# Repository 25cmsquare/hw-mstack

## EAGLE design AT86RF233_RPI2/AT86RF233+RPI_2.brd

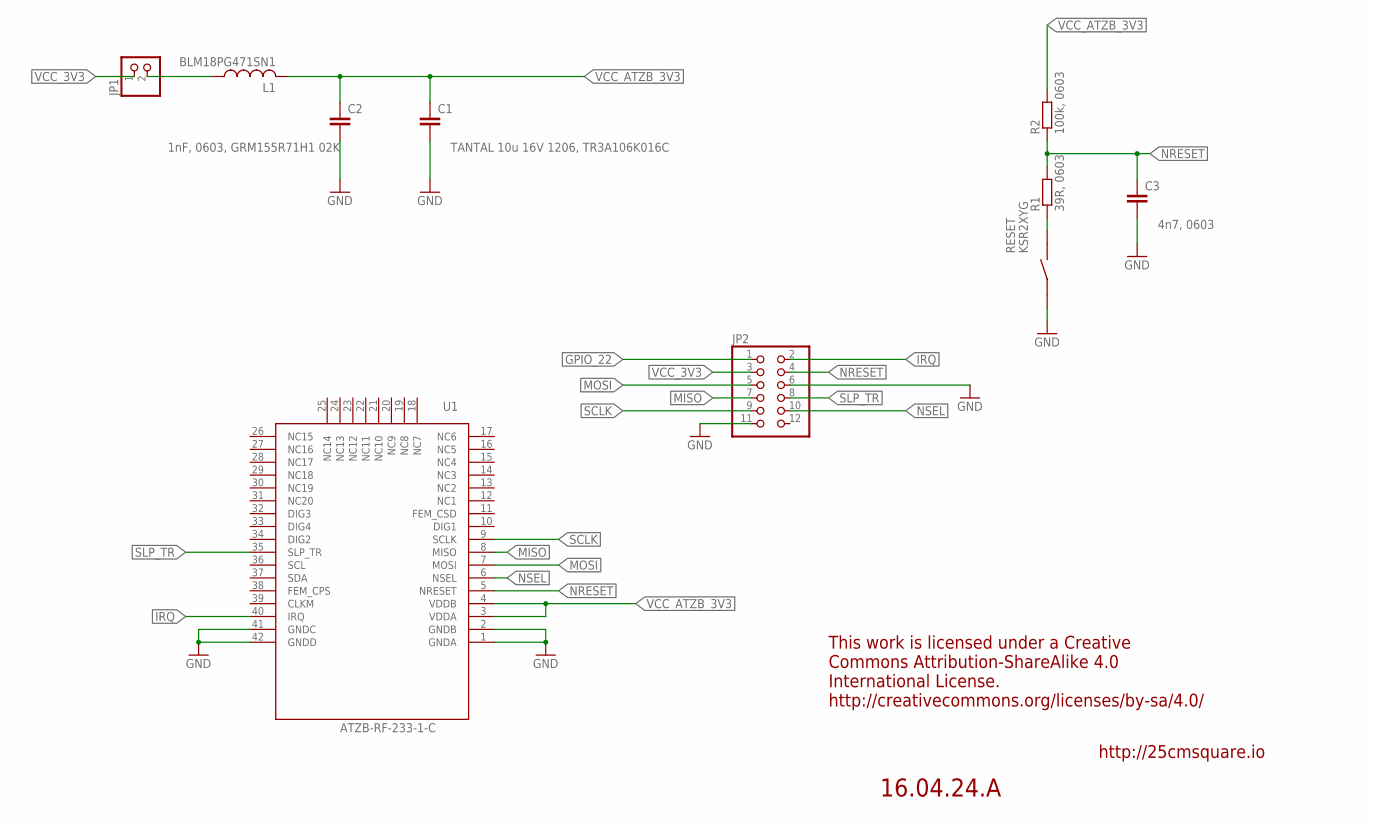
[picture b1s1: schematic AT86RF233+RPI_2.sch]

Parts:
C1: TANTAL 10u 16V 1206, TR3A106K016C; C1206K
C2: 1nF, 0603, GRM155R71H1 02K; C0603K
C3: 4n7, 0603; C0603K
JP1: PINHD-1X2; 1X02
JP2: PINHD-2X6; 2X06
L1: BLM18PG471SN1; L0603
R1: 39R, 0603; R0603
R2: 100k, 0603; R0603
RESET: KSR2XYG
U1: ATZB-RF-233-1-C

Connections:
GND: C1.2, C2.2, C3.2, JP2.6, JP2.11, RESET.P$2 (2), U1.1 (GNDA), U1.2 (GNDB), U1.41 (GNDC), U1.42 (GNDD)
GPIO_22: JP2.1
IRQ: JP2.2, U1.40 (IRQ)
MISO: JP2.7, U1.8 (MISO)
MOSI: JP2.5, U1.7 (MOSI)
unnamed: R1.1, RESET.P$1 (1)
unnamed: JP1.2, L1.1
NRESET: C3.1, JP2.4, R1.2, R2.1, U1.5 (NRESET)
NSEL: JP2.10, U1.6 (NSEL)
SCLK: JP2.9, U1.9 (SCLK)
SLP_TR: JP2.8, U1.35 (SLP_TR)
VCC_3V3: JP1.1, JP2.3
VCC_ATZB_3V3: C1.1, C2.1, L1.2, R2.2, U1.3 (VDDA), U1.4 (VDDB)

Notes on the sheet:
This work is licensed under a Creative Commons Attribution-ShareAlike 4.0 International License. http://creativecommons.org/licenses/by-sa/4.0/
http://25cmsquare.io
16.04.24.A

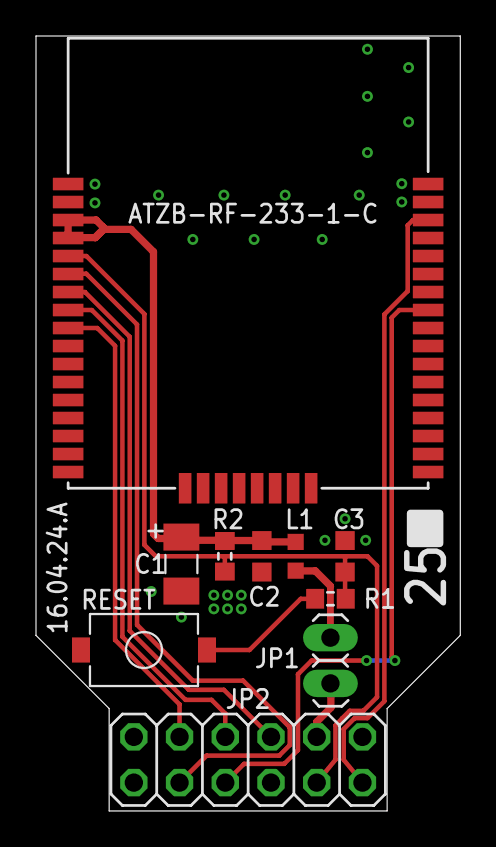
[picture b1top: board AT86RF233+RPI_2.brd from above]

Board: 2 copper layers, 23.6 x 43.1 mm, 10 parts (0 on the bottom side), 12 nets.

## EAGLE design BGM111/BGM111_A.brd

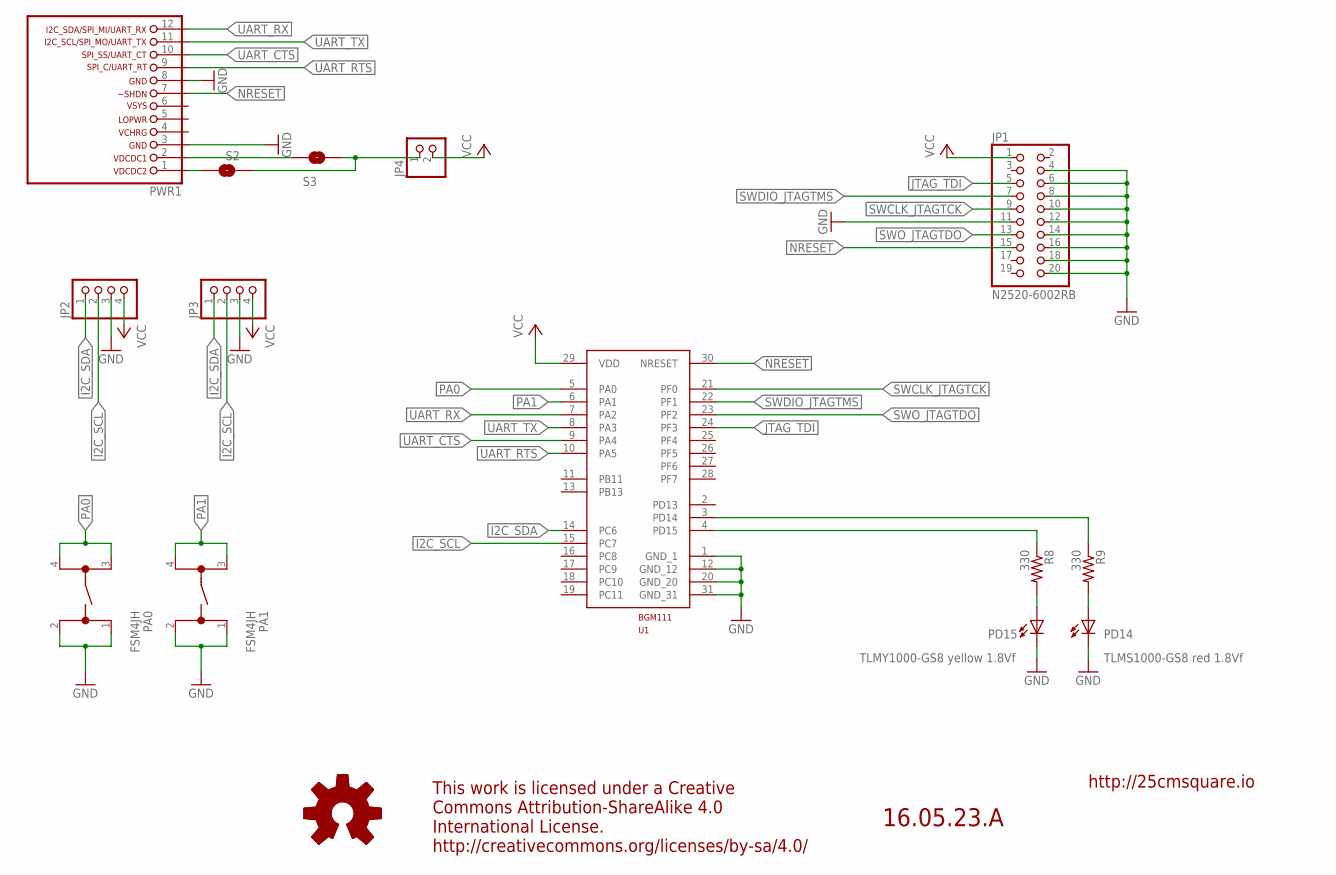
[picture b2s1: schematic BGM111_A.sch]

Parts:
JP1: N2520-6002RB; 2X10
JP2, JP3: PINHD-1X4; 1X04
JP4: PINHD-1X2; 1X02
PA0, PA1: FSM4JH
PD14: TLMS1000-GS8 red 1.8Vf; SML0603
PD15: TLMY1000-GS8 yellow 1.8Vf; SML0603
PWR1: LIWE_12_PIN_PWR; LIWE_12_PIN
R8, R9: 330; R0603
S2, S3: SOLDERJUMPERNC2; SJ_2S-NOTRACE
U1: BGM111
U$1: OSHW_LOGO; OSHW

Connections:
GND: JP1.4, JP1.6, JP1.8, JP1.10, JP1.11, JP1.12, JP1.14, JP1.16, JP1.18, JP1.20, JP2.3, JP3.3, PA0.1, PA0.2, PA1.1, PA1.2, PD14.C, PD15.C, PWR1.3, PWR1.8, U1.1 (GND_1), U1.12 (GND_12), U1.20 (GND_20), U1.31 (GND_31)
I2C_SCL: JP2.2, JP3.2, U1.15 (PC7)
I2C_SDA: JP2.1, JP3.1, U1.14 (PC6)
JTAG_TDI: JP1.5, U1.24 (PF3)
unnamed: PWR1.1, S2.1
unnamed: PWR1.2, S3.1
unnamed: JP4.1, S2.2, S3.2
unnamed: PD14.A, R9.2
unnamed: PD15.A, R8.2
NRESET: JP1.15, PWR1.7, U1.30 (NRESET)
PA0: PA0.3, PA0.4, U1.5 (PA0)
PA1: PA1.3, PA1.4, U1.6 (PA1)
PF5: R9.1, U1.3 (PD14)
PF6: R8.1, U1.4 (PD15)
SWCLK_JTAGTCK: JP1.9, U1.21 (PF0)
SWDIO_JTAGTMS: JP1.7, U1.22 (PF1)
SWO_JTAGTDO: JP1.13, U1.23 (PF2)
UART_CTS: PWR1.10, U1.9 (PA4)
UART_RTS: PWR1.9, U1.10 (PA5)
UART_RX: PWR1.12, U1.7 (PA2)
UART_TX: PWR1.11, U1.8 (PA3)
VCC: JP1.1, JP2.4, JP3.4, JP4.2, U1.29 (VDD)

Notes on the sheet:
This work is licensed under a Creative Commons Attribution-ShareAlike 4.0 International License. http://creativecommons.org/licenses/by-sa/4.0/
16.05.23.A
http://25cmsquare.io

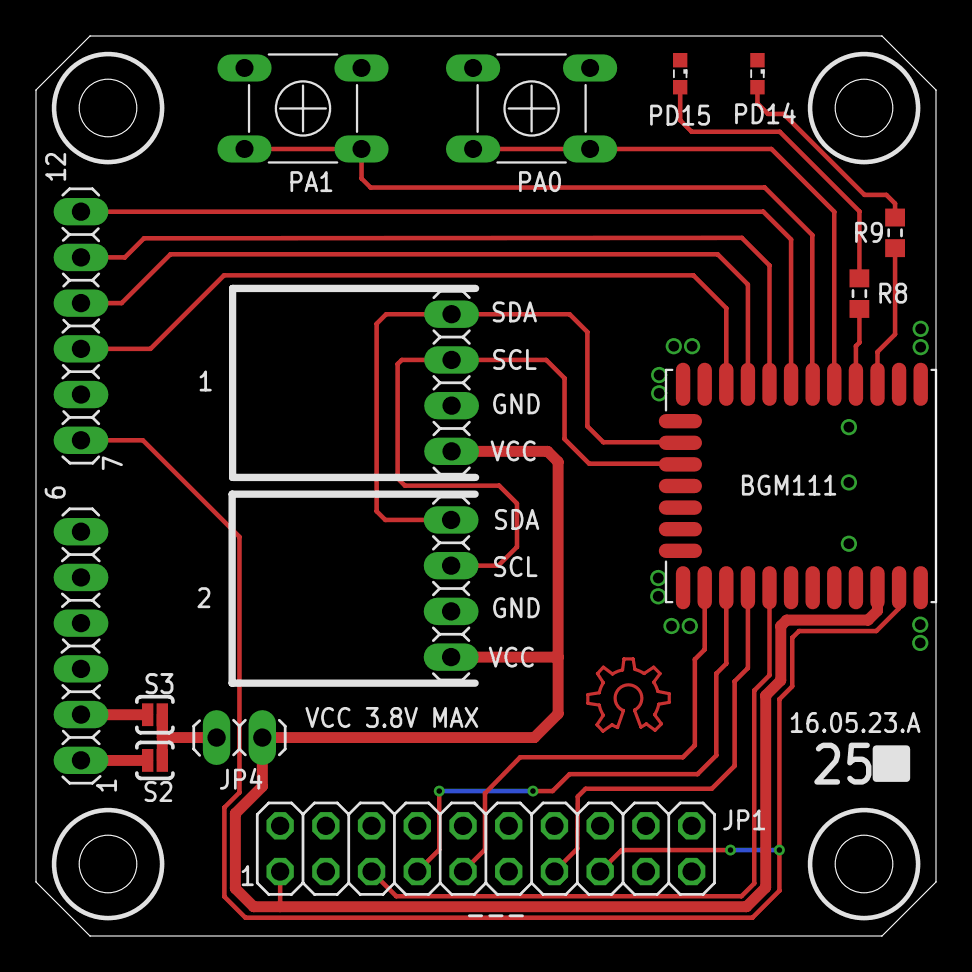
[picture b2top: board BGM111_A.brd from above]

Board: 2 copper layers, 50.0 x 50.0 mm, 15 parts (0 on the bottom side), 22 nets.

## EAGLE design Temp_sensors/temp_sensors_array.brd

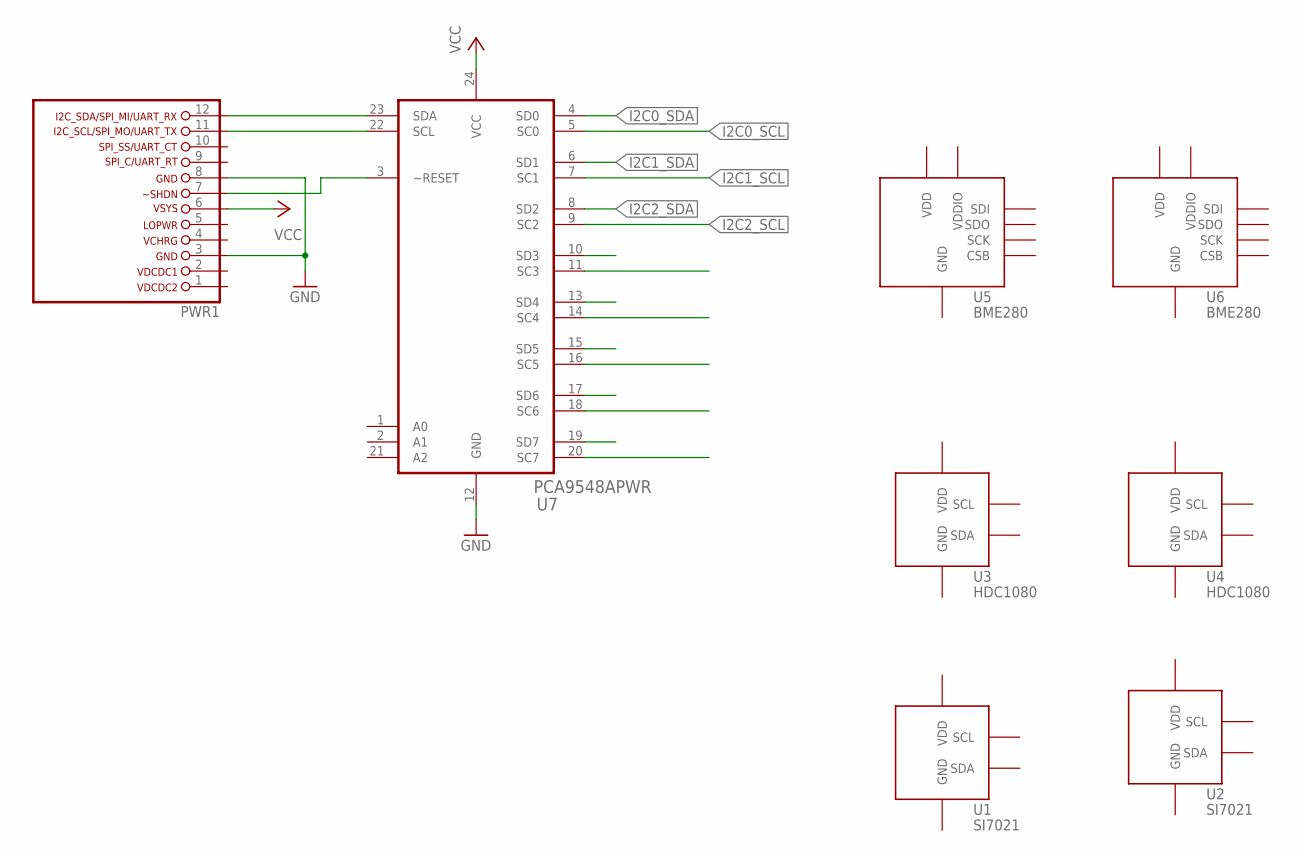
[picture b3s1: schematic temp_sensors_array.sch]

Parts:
PWR1: LIWE_12_PIN_PWR; LIWE_12_PIN
U1, U2: SI7021
U3, U4: HDC1080; SI7021
U5, U6: BME280; BME1080
U7: PCA9548APWR; SOP65P640X120-24N

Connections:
GND: PWR1.3, PWR1.8, U1.2 (GND), U2.2 (GND), U3.2 (GND), U4.2 (GND), U5.1 (GND), U5.7 (GND), U6.1 (GND), U6.7 (GND), U7.12 (GND)
I2C0_SCL: U7.5 (SC0)
I2C0_SDA: U7.4 (SD0)
I2C1_SCL: U7.7 (SC1)
I2C1_SDA: U7.6 (SD1)
I2C2_SCL: U7.9 (SC2)
I2C2_SDA: U7.8 (SD2)
unnamed: PWR1.12, U7.23 (SDA)
unnamed: PWR1.11, U7.22 (SCL)
unnamed: PWR1.7, U7.3 (~RESET)
VCC: PWR1.6, U7.24 (VCC)
VDD: U1.5 (VDD), U2.5 (VDD), U3.5 (VDD), U4.5 (VDD), U5.8 (VDD), U6.8 (VDD)
VDDIO: U5.6 (VDDIO), U6.6 (VDDIO)

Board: 2 copper layers, 8 parts (0 on the bottom side), 7 nets, no tracks yet.

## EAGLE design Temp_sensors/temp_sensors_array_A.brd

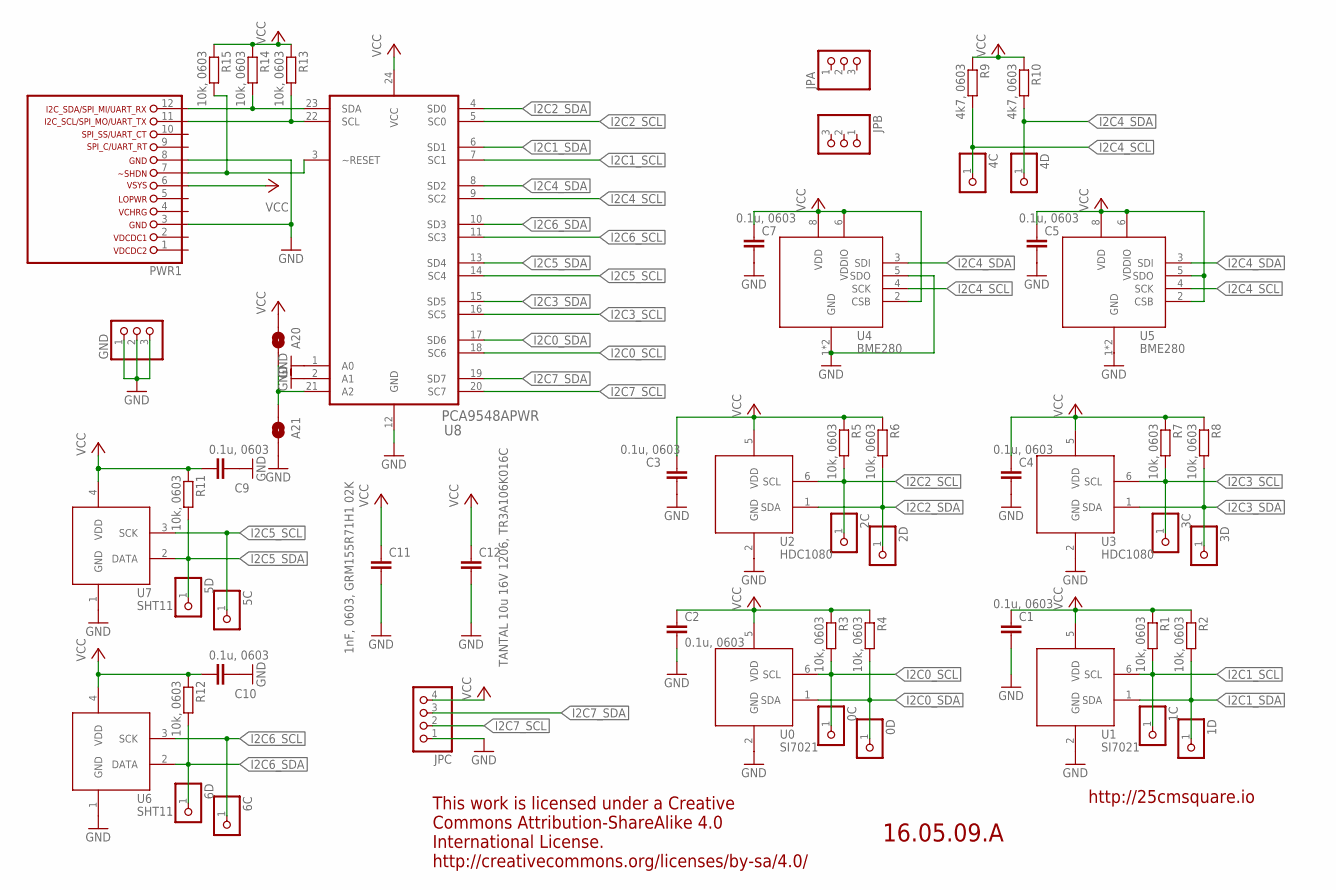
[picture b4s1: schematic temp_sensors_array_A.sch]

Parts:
0C, 0D, 1C, 1D, 2C, 2D, 3C, 3D, 4C, 4D, 5C, 5D, 6C, 6D: PINHD-1X1; 1X01
A20, A21: SOLDERJUMPERNO; SJ_2S-NO
C1, C2, C3, C4, C5, C7, C9, C10: 0.1u, 0603; C0603K
C11: 1nF, 0603, GRM155R71H1 02K; C0603K
C12: TANTAL 10u 16V 1206, TR3A106K016C; C1206K
GND: PINHD-1X3; 1X03
JPA: PINHD-1X3; 1X03
JPB: PINHD-1X3; 1X03
JPC: PINHD-1X4; 1X04
PWR1: LIWE_12_PIN_PWR; LIWE_12_PIN
R1, R2, R3, R4, R5, R6, R7, R8, R11, R12, R13, R14, R15: 10k, 0603; R0603
R9, R10: 4k7, 0603; R0603
U0, U1: SI7021
U2, U3: HDC1080; SI7021
U4, U5: BME280; BME1080
U6, U7: SHT11; SHT1X
U8: PCA9548APWR; SOP65P640X120-24N

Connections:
GND: A21.2, C1.2, C2.2, C3.2, C4.2, C5.2, C7.2, C9.2, C10.2, C11.2, C12.2, GND.1, GND.2, GND.3, JPC.1, PWR1.3, PWR1.8, U0.2 (GND), U1.2 (GND), U2.2 (GND), U3.2 (GND), U4.1 (GND), U4.5 (SDO), U4.7 (GND), U5.1 (GND), U5.7 (GND), U6.1 (GND), U7.1 (GND), U8.1 (A0), U8.2 (A1), U8.12 (GND)
I2C0_SCL: 0C.1, R3.2, U0.6 (SCL), U8.18 (SC6)
I2C0_SDA: 0D.1, R4.2, U0.1 (SDA), U8.17 (SD6)
I2C1_SCL: 1C.1, R1.2, U1.6 (SCL), U8.7 (SC1)
I2C1_SDA: 1D.1, R2.2, U1.1 (SDA), U8.6 (SD1)
I2C2_SCL: 2C.1, R5.2, U2.6 (SCL), U8.5 (SC0)
I2C2_SDA: 2D.1, R6.2, U2.1 (SDA), U8.4 (SD0)
I2C3_SCL: 3C.1, R7.2, U3.6 (SCL), U8.16 (SC5)
I2C3_SDA: 3D.1, R8.2, U3.1 (SDA), U8.15 (SD5)
I2C4_SCL: 4C.1, R9.2, U4.4 (SCK), U5.4 (SCK), U8.9 (SC2)
I2C4_SDA: 4D.1, R10.2, U4.3 (SDI), U5.3 (SDI), U8.8 (SD2)
I2C5_SCL: 5C.1, U7.3 (SCK), U8.14 (SC4)
I2C5_SDA: 5D.1, R11.2, U7.2 (DATA), U8.13 (SD4)
I2C6_SCL: 6C.1, U6.3 (SCK), U8.11 (SC3)
I2C6_SDA: 6D.1, R12.2, U6.2 (DATA), U8.10 (SD3)
I2C7_SCL: JPC.2, U8.20 (SC7)
I2C7_SDA: JPC.3, U8.19 (SD7)
unnamed: A20.2, A21.1, U8.21 (A2)
NRESET: PWR1.7, R15.2, U8.3 (~RESET)
SCL: PWR1.11, R13.2, U8.22 (SCL)
SDA: PWR1.12, R14.2, U8.23 (SDA)
VCC: A20.1, C1.1, C2.1, C3.1, C4.1, C5.1, C7.1, C9.1, C10.1, C11.1, C12.1, JPC.4, PWR1.6, R1.1, R2.1, R3.1, R4.1, R5.1, R6.1, R7.1, R8.1, R9.1, R10.1, R11.1, R12.1, R13.1, R14.1, R15.1, U0.5 (VDD), U1.5 (VDD), U2.5 (VDD), U3.5 (VDD), U4.2 (CSB), U4.6 (VDDIO), U4.8 (VDD), U5.2 (CSB), U5.5 (SDO), U5.6 (VDDIO), U5.8 (VDD), U6.4 (VDD), U7.4 (VDD), U8.24 (VCC)

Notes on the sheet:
This work is licensed under a Creative Commons Attribution-ShareAlike 4.0 International License. http://creativecommons.org/licenses/by-sa/4.0/
16.05.09.A
http://25cmsquare.io

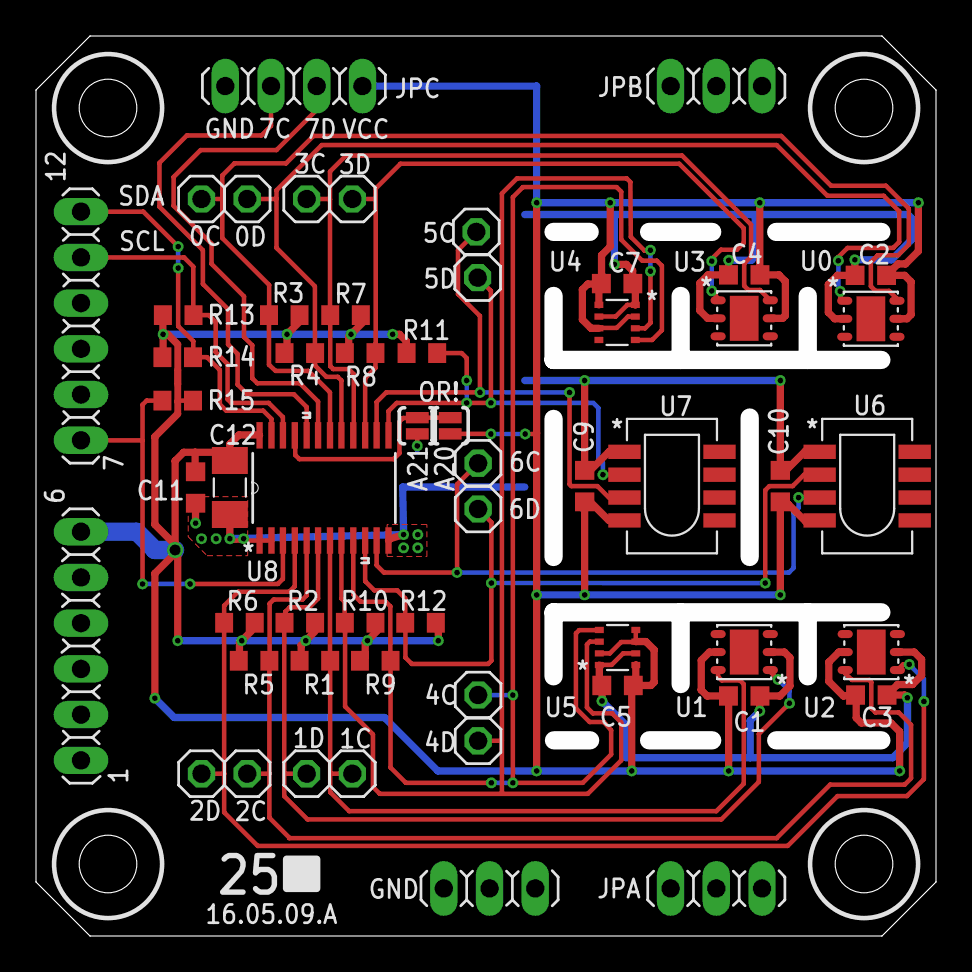
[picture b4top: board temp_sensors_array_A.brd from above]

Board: 2 copper layers, 50.0 x 50.0 mm, 55 parts (0 on the bottom side), 22 nets.

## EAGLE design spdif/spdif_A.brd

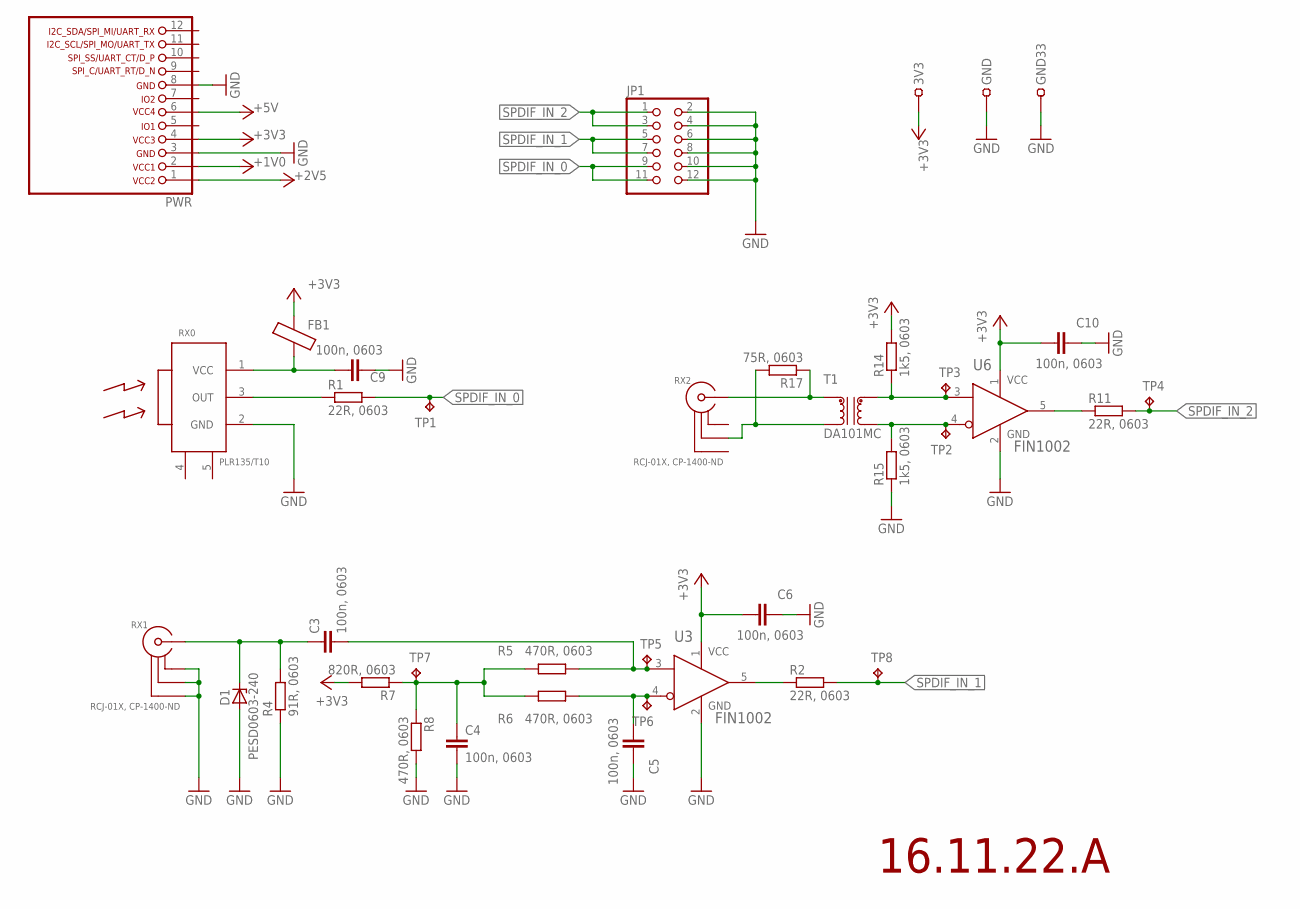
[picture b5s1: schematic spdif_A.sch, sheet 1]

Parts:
3V3: TEST-22-MULTICOMP; TEST_1MM
C3, C4, C5, C6, C9, C10: 100n, 0603; C0603
D1: PESD0603-240; L0603
FB1: FB_0603; L0603
GND, GND33: TEST-22-MULTICOMP; TEST_1MM
JP1: PINHD-2X6/90; 2X06/90
PWR: LIWE_12_PIN_PWR7X7_COMPAT; LIWE_12_PIN_7X7_COMPAT
R1, R2, R11: 22R, 0603; R0603
R4: 91R, 0603; R0603
R5, R6, R8: 470R, 0603; R0603
R7: 820R, 0603; R0603
R14, R15: 1k5, 0603; R0603
R17: 75R, 0603; R0603
RX0: PLR135/T10; PLR135_T10
RX1, RX2: RCJ-01X, CP-1400-ND; RCJ-01X
T1: DA101MC
TP1, TP2, TP3, TP4, TP5, TP6, TP7, TP8: TPB1,27; B1,27
U3, U6: FIN1002; SOT95P280X140-5N

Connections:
+1V0: PWR.2
+2V5: PWR.1
+3V3: 3V3.1, C6.2, C10.2, FB1.2, PWR.4, R7.2, R14.2, U3.1 (VCC), U6.1 (VCC); also elsewhere on the board
+5V: PWR.6
GND: C4.2, C5.1, C6.1, C9.1, C10.1, D1.1 (A), GND.1, GND33.1, JP1.2, JP1.4, JP1.6, JP1.8, JP1.10, JP1.12, PWR.3, PWR.8, R4.1, R8.2, R15.1, RX0.2 (GND), RX1.20 (GND1), RX1.21 (GND2), RX1.22 (GND3), U3.2 (GND), U6.2 (GND); also elsewhere on the board
unnamed: R2.1, U3.5 (ROUT)
unnamed: C3.2, R5.1, TP5.TP, U3.3 (RIN+)
unnamed: C9.2, FB1.1, RX0.1 (VCC)
unnamed: C3.1, D1.2 (C), R4.2, RX1.1 (SIG)
unnamed: R11.1, U6.5 (ROUT)
unnamed: C4.1, R5.2, R6.2, R7.1, R8.1, TP7.TP
unnamed: C5.2, R6.1, TP6.TP, U3.4 (RIN-)
unnamed: R15.2, T1.4, TP2.TP, U6.4 (RIN-)
unnamed: R14.1, T1.6, TP3.TP, U6.3 (RIN+)
unnamed: R17.2, RX2.21 (GND2), T1.3
unnamed: R17.1, RX2.1 (SIG), T1.1
SPDIF0_IN: R1.1, RX0.3 (OUT)
SPDIF_IN_0: JP1.9, JP1.11, R1.2, TP1.TP
SPDIF_IN_1: JP1.5, JP1.7, R2.2, TP8.TP
SPDIF_IN_2: JP1.1, JP1.3, R11.2, TP4.TP

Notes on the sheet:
16.11.22.A

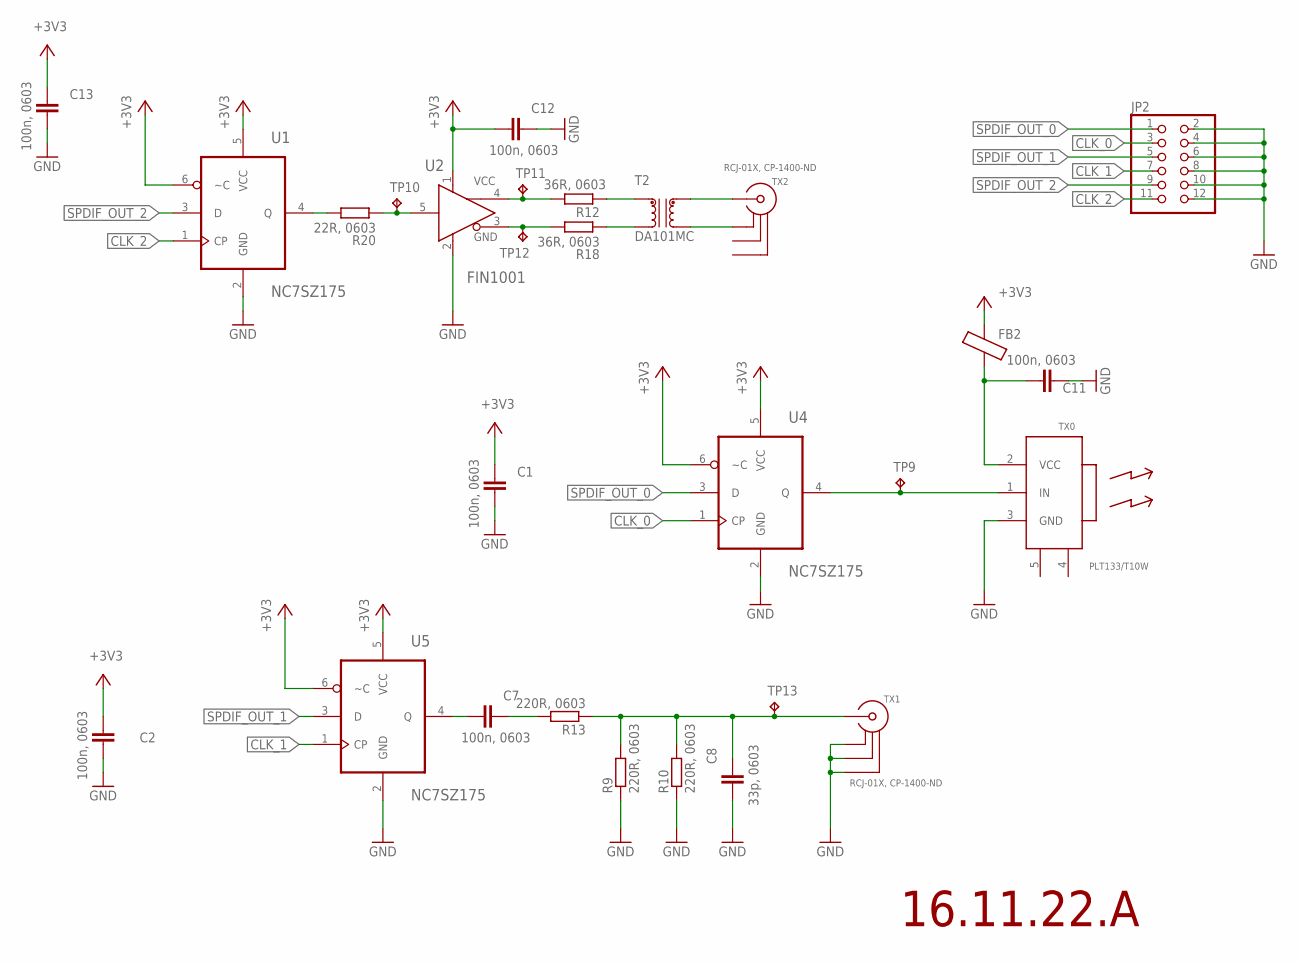
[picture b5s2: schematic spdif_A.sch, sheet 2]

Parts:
C1, C2, C7, C11, C12, C13: 100n, 0603; C0603
C8: 33p, 0603; C0603
FB2: FB_0603; L0603
JP2: PINHD-2X6/90; 2X06/90
R9, R10, R13: 220R, 0603; R0603
R12, R18: 36R, 0603; R0603
R20: 22R, 0603; R0603
T2: DA101MC
TP9, TP10, TP11, TP12, TP13: TPB1,27; B1,27
TX0: PLT133/T10W; PLT133_T10W
TX1, TX2: RCJ-01X, CP-1400-ND; RCJ-01X
U1, U4, U5: NC7SZ175; SOT65P210X110-6N
U2: FIN1001; SOT95P280X140-5N

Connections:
+3V3: C1.2, C2.2, C12.2, C13.2, FB2.2, U1.5 (VCC), U1.6 (~C), U2.1 (VCC), U4.5 (VCC), U4.6 (~C), U5.5 (VCC), U5.6 (~C); also elsewhere on the board
CLK_0: JP2.3, U4.1 (CP)
CLK_1: JP2.7, U5.1 (CP)
CLK_2: JP2.11, U1.1 (CP)
DA_N: R18.1, T2.3
DA_P: R12.1, T2.1
FIN_IN: R20.1, TP10.TP, U2.5 (RIN)
FIN_OUT_N: R18.2, TP12.TP, U2.3 (ROUT-)
FIN_OUT_P: R12.2, TP11.TP, U2.4 (ROUT+)
GND: C1.1, C2.1, C8.2, C11.1, C12.1, C13.1, JP2.2, JP2.4, JP2.6, JP2.8, JP2.10, JP2.12, R9.1, R10.1, TX0.3 (GND), TX1.20 (GND1), TX1.21 (GND2), TX1.22 (GND3), U1.2 (GND), U2.2 (GND), U4.2 (GND), U5.2 (GND); also elsewhere on the board
unnamed: C8.1, R9.2, R10.2, R13.1, TP13.TP, TX1.1 (SIG)
unnamed: C7.1, R13.2
unnamed: C7.2, U5.4 (Q)
Q: R20.2, U1.4 (Q)
SPDIF_OUT_0: JP2.1, U4.3 (D)
SPDIF_OUT_1: JP2.5, U5.3 (D)
SPDIF_OUT_2: JP2.9, U1.3 (D)
TX0_IN: TP9.TP, TX0.1 (IN), U4.4 (Q)
TX0_VCC: C11.2, FB2.1, TX0.2 (VCC)
TX2_N: T2.4, TX2.20 (GND1)
TX2_P: T2.6, TX2.1 (SIG)

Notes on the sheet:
16.11.22.A

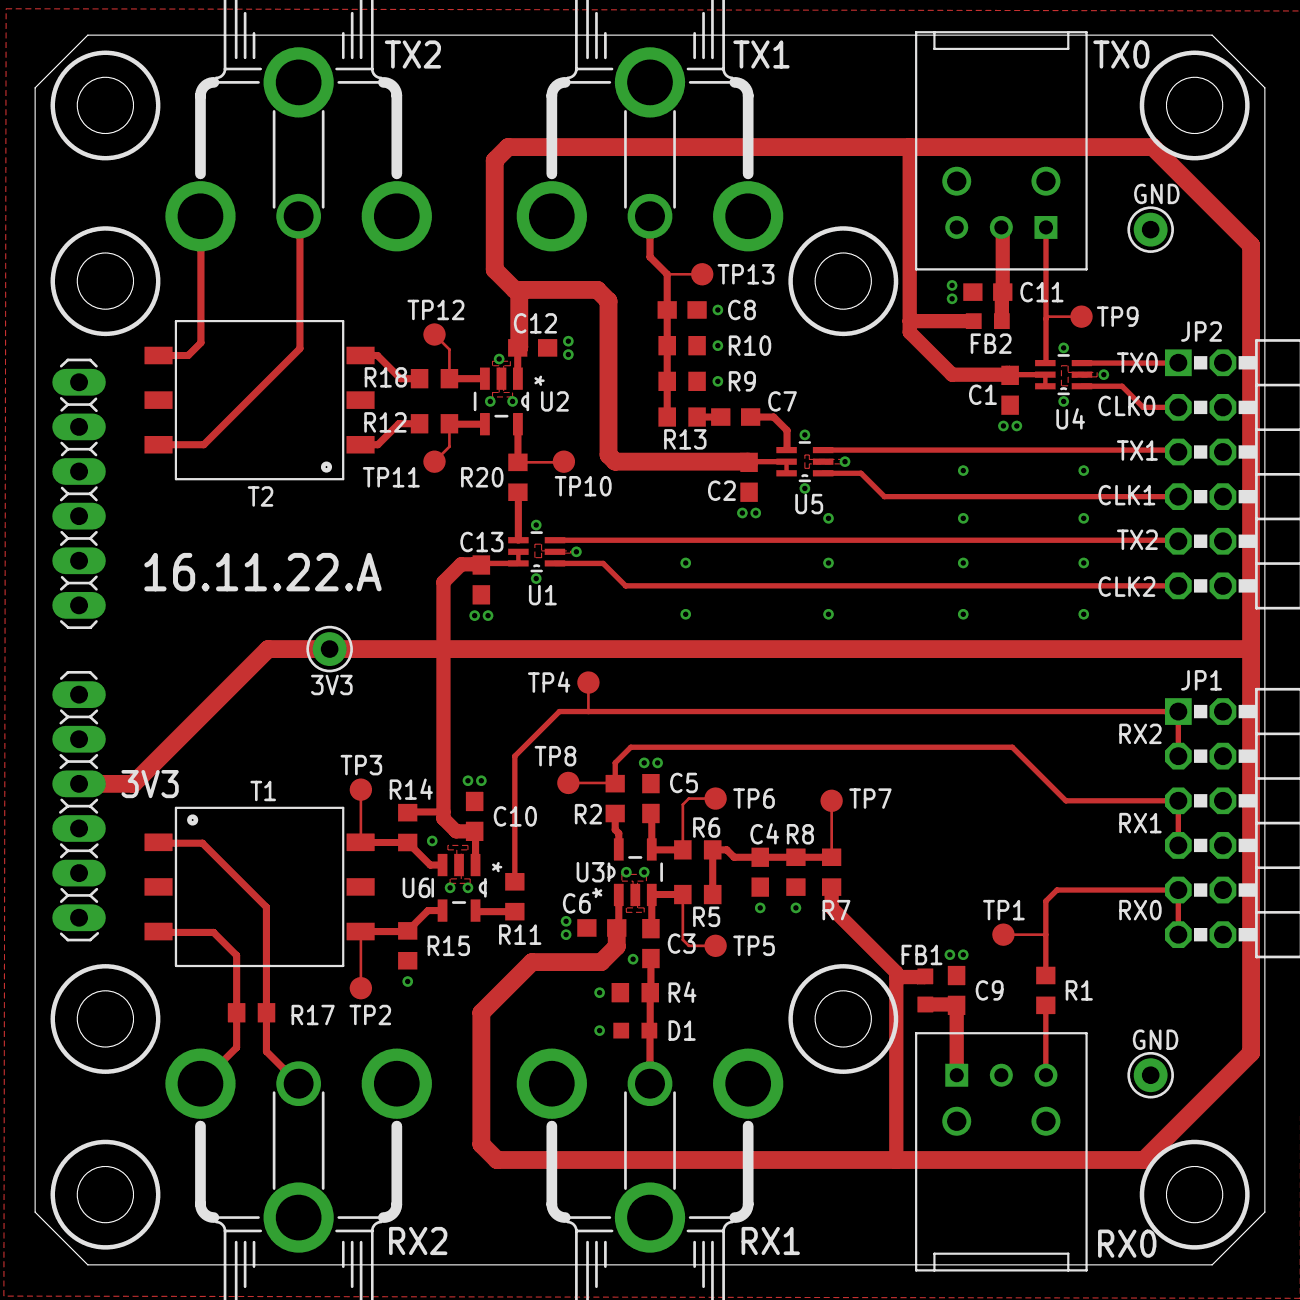
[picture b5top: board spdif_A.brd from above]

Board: 2 copper layers, 70.0 x 70.0 mm, 66 parts (0 on the bottom side), 36 nets.

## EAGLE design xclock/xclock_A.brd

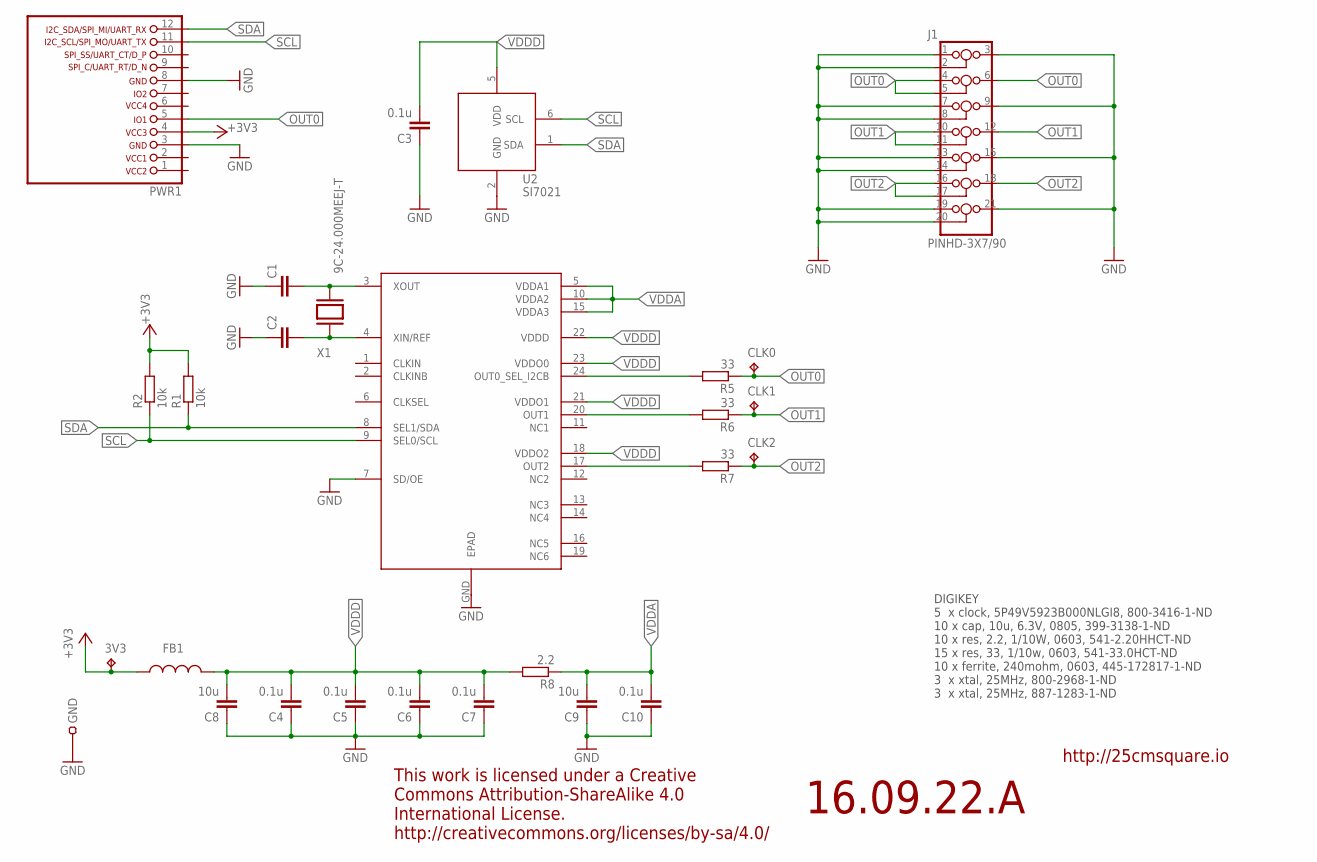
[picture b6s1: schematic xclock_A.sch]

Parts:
3V3: TPB1,27; B1,27
C1, C2: C-EUC0603; C0603
C3, C4, C5, C6, C7, C10: 0.1u; C0603
C8, C9: 10u; C0805
CLK0, CLK1, CLK2: TPB1,27; B1,27
FB1: L0603(1608); L0603
GND: TEST-22-MULTICOMP; TEST_1MM
J1: PINHD-3X7/90; 3X07/90
PWR1: LIWE_12_PIN_PWR; LIWE_12_PIN
R1, R2: 10k; R0603
R5, R6, R7: 33; R0603
R8: 2.2; R0603
U1: 5P49V5923; VFQFPN_24_4X4
U2: SI7021
X1: 9C-24.000MEEJ-T; TXC_SMD_HC-49S

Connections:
+3V3: 3V3.TP, FB1.1, PWR1.4, R1.2, R2.2
GND: C1.1, C2.1, C3.1, C4.1, C5.1, C6.1, C7.1, C8.1, C9.1, C10.1, GND.1, J1.1, J1.2, J1.3, J1.7, J1.8, J1.9, J1.13, J1.14, J1.15, J1.19, J1.20, J1.21, PWR1.3, PWR1.8, U1.7 (SD/OE), U1.GND (EPAD), U2.2 (GND)
unnamed: R5.2, U1.24 (OUT0_SEL_I2CB)
unnamed: R6.2, U1.20 (OUT1)
unnamed: R7.2, U1.17 (OUT2)
OUT0: CLK0.TP, J1.4, J1.5, J1.6, PWR1.5, R5.1
OUT1: CLK1.TP, J1.10, J1.11, J1.12, R6.1
OUT2: CLK2.TP, J1.16, J1.17, J1.18, R7.1
SCL: PWR1.11, R2.1, U1.9 (SEL0/SCL), U2.6 (SCL)
SDA: PWR1.12, R1.1, U1.8 (SEL1/SDA), U2.1 (SDA)
VDDA: C9.2, C10.2, R8.1, U1.5 (VDDA1), U1.10 (VDDA2), U1.15 (VDDA3)
VDDD: C3.2, C4.2, C5.2, C6.2, C7.2, C8.2, FB1.2, R8.2, U1.18 (VDDO2), U1.21 (VDDO1), U1.22 (VDDD), U1.23 (VDDO0), U2.5 (VDD)
XIN: C2.2, U1.4 (XIN/REF), X1.1
XOUT: C1.2, U1.3 (XOUT), X1.2

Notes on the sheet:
16.09.22.A
DIGIKEY 5 x clock, 5P49V5923B000NLGI8, 800-3416-1-ND 10 x cap, 10u, 6.3V, 0805, 399-3138-1-ND 10 x res, 2.2, 1/10W, 0603, 541-2.20HHCT-ND 15 x res, 33, 1/10w, 0603, 541-33.0HCT-ND 10 x ferrite, 240mohm, 0603, 445-172817-1-ND 3 x xtal, 25MHz, 800-2968-1-ND 3 x xtal, 25MHz, 887-1283-1-ND
This work is licensed under a Creative Commons Attribution-ShareAlike 4.0 International License. http://creativecommons.org/licenses/by-sa/4.0/
http://25cmsquare.io

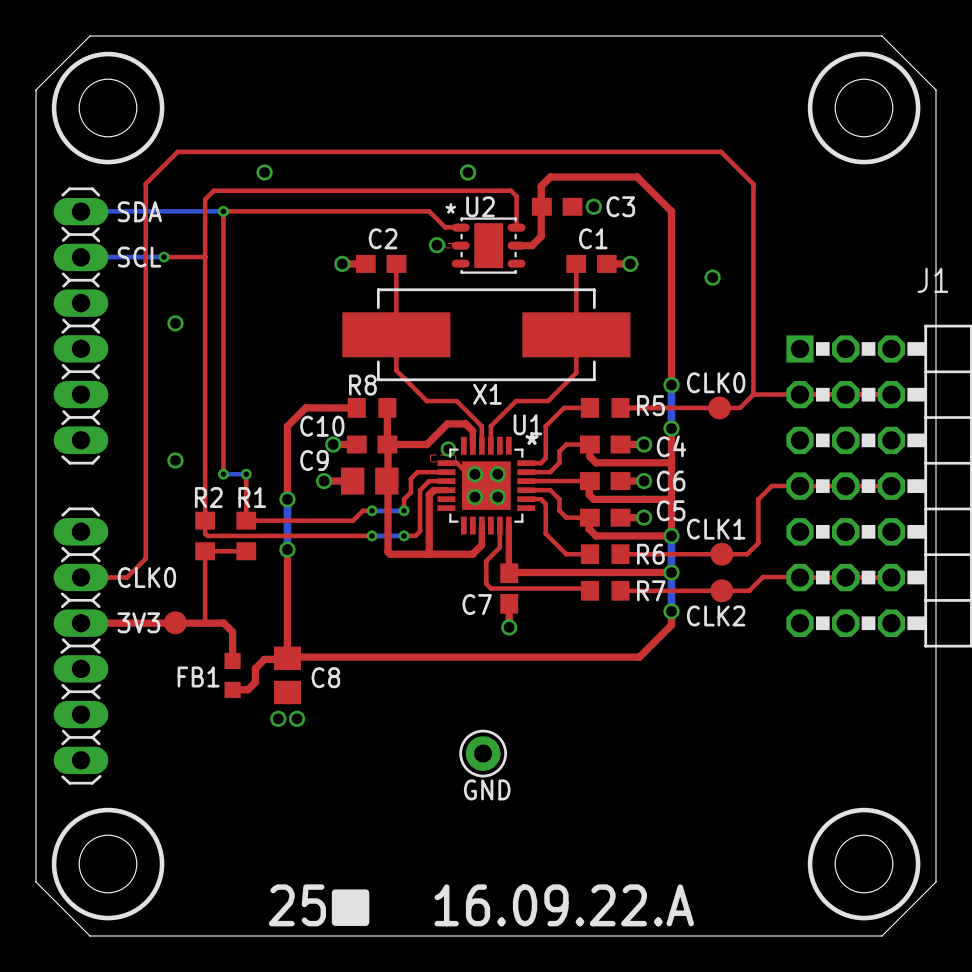
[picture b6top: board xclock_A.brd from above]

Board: 2 copper layers, 50.0 x 50.0 mm, 27 parts (0 on the bottom side), 14 nets.

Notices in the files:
parts and their libraries:
SparkFun-Passives: Licensing: Creative Commons ShareAlike 4.0 International - https://creativecommons.org/licenses/by-sa/4.0
